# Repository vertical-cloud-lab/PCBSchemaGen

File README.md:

# PCBSchemaGen

LLM-based PCB schematic generation with automated topology verification.

# Installation

PCBSchemaGen requires:
- Python >= 3.10
- KiCad 9 (with pcbnew Python bindings)
- Node.js + `netlistsvg` (for schematic SVG generation)
- OpenAI-compatible API access

## Step 1: Install KiCad 9

Follow the official KiCad installation guide for your platform:

**https://www.kicad.org/download/**

After installation, verify KiCad and pcbnew:
```bash
kicad-cli --version
python3 -c "import pcbnew; print(pcbnew.GetBuildVersion())"
```

## Step 2: Install Python Dependencies

```bash
pip install openai pandas skidl networkx cairosvg Pillow
```

## Step 3: Install netlistsvg

SKiDL's `generate_svg()` shells out to the `netlistsvg` CLI. Without it, SVG
generation (and therefore the sample verification suite) fails. Install it with
npm (requires Node.js):

```bash
npm install -g netlistsvg
netlistsvg --help   # verify it is on your PATH
```

## Step 4: Environment Check

```bash
cd "sample design"
XDG_DATA_HOME=$(pwd)/../.xdg python3 run_samples_test.py
```

All 17 tasks should print `[PASS]`. If not, check your KiCad and `netlistsvg` installation.

# Quick Start

```bash
cd task
XDG_DATA_HOME=$(pwd)/.. python3 run.py \
  --task_id 1 \
  --model gpt-4o \
  --api_key "YOUR_API_KEY" \
  --base_url https://openrouter.ai/api/v1
```

This generates a circuit for Task 1 (voltage divider).

# API Keys

Any OpenAI-compatible API works. We recommend [OpenRouter](https://openrouter.ai):
1. Create account at https://openrouter.ai
2. Get API key from dashboard
3. Use with `--base_url https://openrouter.ai/api/v1`

You can also point directly at a provider's OpenAI-compatible endpoint. For
example, Anthropic's endpoint works with this benchmark:

```bash
cd task
OPENAI_API_KEY="YOUR_ANTHROPIC_KEY" XDG_DATA_HOME=$(pwd)/.. python3 run.py \
  --task_id 1 \
  --model claude-sonnet-4-6 \
  --base_url https://api.anthropic.com/v1/
```

Note: some newer Anthropic models (e.g. `claude-opus-4-8`) reject the
`temperature` parameter; use a model that accepts it (e.g. `claude-sonnet-4-6`)
or pass `--temperature` only with models that support it.

# Benchmark

- **Task definitions**: `benchmark.tsv` (23 tasks across 3 difficulty levels)
- **Reference designs**: `sample design/p*.py`
- **Component library**: `component.json`, `kg_component.json`
- **KiCad symbols/footprints**: `library/`

## Task Difficulty Levels

| Level | Tasks | Description |
|-------|-------|-------------|
| Easy | P1-P6 | Voltage dividers, LDOs, sensing circuits |
| Medium | P7-P16 | Half-bridge stages, gate drivers, isolated DC-DC |
| Hard | P17-P23 | Multi-switch converters (sync buck, DAB, LLC, 3-phase) |

# Example Output

The `example_output/` directory contains a successful run of Task 17 (Synchronous Buck Converter):

| File | Description |
|------|-------------|
| `attempt_1_skidl.py` | LLM-generated SKiDL code |
| `attempt_1.svg` | Circuit schematic visualization |
| `task_17_stats.json` | Run statistics (tokens, time, status) |
| `task_17_output.txt` | Full LLM output with chain-of-thought |
| `extracted_task_17.*` | Final artifacts (netlist, KiCad project) |

# Project Structure

```
PCBSchemaGen/
├── task/
│   ├── run.py                  # Single task runner
│   ├── run_feedback_trials.py  # Batch experiments
│   ├── topo/                   # Verification pipeline
│   └── prompt_template*.md     # LLM prompts
├── sample design/              # Ground truth implementations
├── library/                    # KiCad symbols & footprints
├── example_output/             # Example Task 17 output
├── benchmark.tsv               # Task definitions
├── component.json              # Component pin definitions
└── kg_component.json           # Component constraints
```

# Batch Experiments

To run multiple tasks with multiple trials:

```bash
cd task
XDG_DATA_HOME=$(pwd)/.. python3 run_feedback_trials.py \
  --task-range 1-16 \
  --trials 15 \
  --model gpt-4o \
  --api_key "YOUR_API_KEY" \
  --base_url https://openrouter.ai/api/v1 \
  --feedbacks full \
  --parallel-threads 8
```

Results are saved to `task/feedback_runs/`.

# Citation

If you find this work helpful, please cite our paper:

```bibtex
@misc{zou2026pcbschemagen,
      title={PCBSchemaGen: Constraint-Guided Schematic Design via LLM for Printed Circuit Boards (PCB)}, 
      author={Huanghaohe Zou and Peng Han and Emad Nazerian and Alex Q. Huang},
      year={2026},
      eprint={2602.00510},
      archivePrefix={arXiv},
      primaryClass={cs.AI},
      url={[https://arxiv.org/abs/2602.00510](https://arxiv.org/abs/2602.00510)}, 
}

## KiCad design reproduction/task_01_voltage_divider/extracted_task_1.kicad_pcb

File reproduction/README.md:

# Reproduction Artifacts

End-to-end run artifacts from reproducing two benchmark tasks with the full
PCBSchemaGen pipeline (LLM generation → ERC → topology verification → KiCad
artifact generation). Both runs used the OpenAI-compatible Anthropic endpoint
(`--base_url https://api.anthropic.com/v1/`) with model `claude-sonnet-4-6`.

| Task | Description | Level | Result | Attempts | Components |
|------|-------------|-------|--------|----------|-----------|
| [Task 1](task_01_voltage_divider) | Resistor divider (60 V → 3.3 V sense) | Easy | PASS | 1 | 3 |
| [Task 17](task_17_sync_buck) | Synchronous buck converter | Hard | PASS | 2 | 80 |
| [powder-doser test module](powder_doser_test_module) | Single-Pico-W bench rig ([powder-doser PR #61](https://github.com/vertical-cloud-lab/powder-doser/pull/61)) | External | PASS | 3 | 14 |

Task 17 is the paper's flagship example (compare with [`../example_output/`](../example_output)).
It passed on the second attempt: the first attempt was rejected by the topology
verifier (insufficient output capacitors) and the feedback loop drove the fix.

The [powder-doser test module](powder_doser_test_module) is a real external
design (a microcontroller/breakout board rather than a power-electronics
topology) used to exercise the pipeline outside the benchmark; see its
[README](powder_doser_test_module/README.md) for provenance and the
generation loop. Its
[`CELUS_EVALUATION.md`](powder_doser_test_module/CELUS_EVALUATION.md) assesses
how usable the generated files are for import into a component-driven
board-synthesis tool ([CELUS](https://celus.io)) and demonstrates a re-prompt
that adds the missing sourcing metadata (MPNs, datasheets, real footprints, BOM,
block diagram).

## How these were generated

```bash
cd task
OPENAI_API_KEY="YOUR_KEY" XDG_DATA_HOME=$(pwd)/.. python3 run.py \
  --task_id 1 \
  --model claude-sonnet-4-6 \
  --base_url https://api.anthropic.com/v1/ \
  --num_of_retry 3
# results land in task/p1_results/ (and task/p17_results/ for --task_id 17)
```

## Files (per task)

| File | Description |
|------|-------------|
| `extracted_task_*.png` | Schematic render (PNG, rendered from the SVG) |
| `extracted_task_*.svg` | Schematic render (vector) |
| `extracted_task_*.kicad_pcb` | KiCad PCB model |
| `extracted_task_*.kicad_pro` / `.kicad_prl` | KiCad project files |
| `extracted_task_*.net` | KiCad netlist |
| `extracted_task_*.erc` | Electrical rule check report |
| `extracted_task_*.py` | Final SKiDL source (with artifact-generation wrapper) |
| `attempt_*_skidl.py` | Per-attempt LLM-generated SKiDL code |
| `attempt_*.svg` | Per-attempt intermediate schematic render |
| `task_*_output.txt` | Full LLM response (chain-of-thought + code) |
| `task_*_stats.json` | Run statistics (tokens, timing, status) |

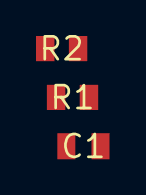
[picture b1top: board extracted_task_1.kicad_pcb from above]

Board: 2 copper layers, 3 parts (0 on the bottom side), 2 nets, no tracks yet.

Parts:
C1: 100nF; C_0805
R1: 100k; R_0805
R2: 10k; R_0805

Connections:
GND: C1.2, R2.2
VSENSE: C1.1, R1.2, R2.1

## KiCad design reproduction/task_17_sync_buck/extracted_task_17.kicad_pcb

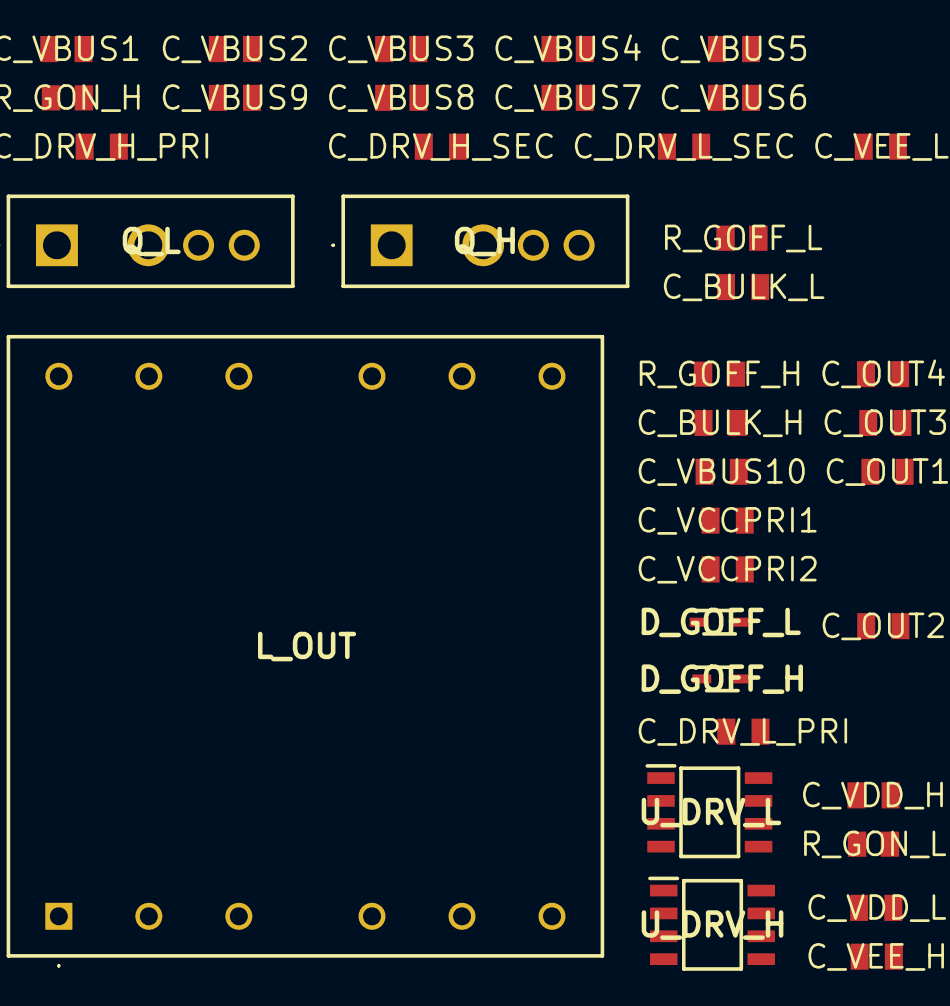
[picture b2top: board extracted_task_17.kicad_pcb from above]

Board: 2 copper layers, 37 parts (0 on the bottom side), 18 nets, no tracks yet.

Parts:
C_BULK_H: 10uF; C_0805
C_BULK_L: 10uF; C_0805
C_DRV_H_PRI: 100nF; C_0805
C_DRV_H_SEC: 100nF; C_0805
C_DRV_L_PRI: 100nF; C_0805
C_DRV_L_SEC: 100nF; C_0805
C_OUT1, C_OUT2, C_OUT3: 100uF; C_0805
C_OUT4: 100nF; C_0805
C_VBUS1, C_VBUS2, C_VBUS3, C_VBUS4, C_VBUS5, C_VBUS6, C_VBUS7, C_VBUS8: 100nF; C_0805
C_VBUS9, C_VBUS10: 10uF; C_0805
C_VCCPRI1: 100nF; C_0805
C_VCCPRI2: 10uF; C_0805
C_VDD_H: 100nF; C_0805
C_VDD_L: 100nF; C_0805
C_VEE_H: 100nF; C_0805
C_VEE_L: 100nF; C_0805
D_GOFF_H: D; BAT165
D_GOFF_L: D; BAT165
L_OUT: 10uH; Inductor_power
Q_H: IMZA65R015M2H
Q_L: IMZA65R015M2H
R_GOFF_H: 2R2; R_0805
R_GOFF_L: 2R2; R_0805
R_GON_H: 10R; R_0805
R_GON_L: 10R; R_0805
U_DRV_H: UCC5390E
U_DRV_L: UCC5390E

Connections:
DRV_H_OUT: R_GOFF_H.2, R_GON_H.1, U_DRV_H.6
DRV_L_OUT: R_GOFF_L.2, R_GON_L.1, U_DRV_L.6
GATE_H: D_GOFF_H.2, Q_H.4, R_GON_H.2
GATE_L: D_GOFF_L.2, Q_L.4, R_GON_L.2
GND_PRI: C_DRV_H_PRI.2, C_DRV_L_PRI.2, C_VCCPRI1.2, C_VCCPRI2.2, U_DRV_H.3, U_DRV_H.4, U_DRV_L.3, U_DRV_L.4
KS_H: C_DRV_H_SEC.2, C_VDD_H.2, C_VEE_H.1, Q_H.3, U_DRV_H.7
KS_L: C_DRV_L_SEC.2, C_VDD_L.2, C_VEE_L.1, Q_L.3, U_DRV_L.7
unnamed: D_GOFF_H.1, R_GOFF_H.1
unnamed: D_GOFF_L.1, R_GOFF_L.1
PGND: C_OUT1.2, C_OUT2.2, C_OUT3.2, C_OUT4.2, C_VBUS1.2, C_VBUS2.2, C_VBUS3.2, C_VBUS4.2, C_VBUS5.2, C_VBUS6.2, C_VBUS7.2, C_VBUS8.2, C_VBUS9.2, C_VBUS10.2, Q_L.2
VCC_PRI: C_DRV_H_PRI.1, C_DRV_L_PRI.1, C_VCCPRI1.1, C_VCCPRI2.1, U_DRV_H.1, U_DRV_L.1
VDD_H: C_BULK_H.1, C_DRV_H_SEC.1, C_VDD_H.1, U_DRV_H.5
VDD_L: C_BULK_L.1, C_DRV_L_SEC.1, C_VDD_L.1, U_DRV_L.5
VEE_H: C_BULK_H.2, C_VEE_H.2, U_DRV_H.8
VEE_L: C_BULK_L.2, C_VEE_L.2, U_DRV_L.8
VIN: C_VBUS1.1, C_VBUS2.1, C_VBUS3.1, C_VBUS4.1, C_VBUS5.1, C_VBUS6.1, C_VBUS7.1, C_VBUS8.1, C_VBUS9.1, C_VBUS10.1, Q_H.1
VOUT: C_OUT1.1, C_OUT2.1, C_OUT3.1, C_OUT4.1, L_OUT.7, L_OUT.8, L_OUT.9, L_OUT.10, L_OUT.11, L_OUT.12
VSW: L_OUT.1, L_OUT.2, L_OUT.3, L_OUT.4, L_OUT.5, L_OUT.6, Q_H.2, Q_L.1

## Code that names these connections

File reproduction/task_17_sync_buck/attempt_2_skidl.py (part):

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# High-side gate resistor network (turn-on / turn-off)
# ─────────────────────────────────────────────
drv_h_out = Net("DRV_H_OUT")
drv_h[6] += drv_h_out        # OUT pin of high-side driver

gate_h = Net("GATE_H")

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
# Anti-parallel diode: conducts during turn-off (gate discharging back to driver)
# D pin1=K(Anode label), pin2=A(Cathode label) per component definition
d_goff_h[2] += gate_h        # pin2(A) at gate node
d_goff_h[1] += r_goff_h[1]  # pin1(K) toward driver side
r_goff_h[2] += drv_h_out

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# Low-side gate resistor network (turn-on / turn-off)
# ─────────────────────────────────────────────
drv_l_out = Net("DRV_L_OUT")
drv_l[6] += drv_l_out        # OUT pin of low-side driver

gate_l = Net("GATE_L")

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d_goff_l = Part("test", "D", footprint="test:BAT165")
d_goff_l.ref = "D_GOFF_L"

d_goff_l[2] += gate_l        # pin2(A) at gate node
d_goff_l[1] += r_goff_l[1]  # pin1(K) toward driver side
r_goff_l[2] += drv_l_out

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# ─────────────────────────────────────────────
# Output LC filter
# ─────────────────────────────────────────────
# Power inductor: pins 1-6 = Terminal A (VSW side), pins 7-12 = Terminal B (VOUT side)
l_out = Part("test", "Inductor_power", footprint="test:Inductor_power")
l_out.ref = "L_OUT"
l_out.value = "10uH"

# Connect all A-side pins to VSW
l_out[1]  += vsw
l_out[2]  += vsw
l_out[3]  += vsw
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l_out[5]  += vsw
l_out[6]  += vsw

# Connect all B-side pins to VOUT
l_out[7]  += vout
l_out[8]  += vout
l_out[9]  += vout
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
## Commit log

2026-06-08 Initial plan
2026-06-08 Set up plan for test run of PCBSchemaGen
2026-06-08 Document required netlistsvg dependency; ignore run artifacts
2026-06-08 Commit reproduction artifacts for Task 1 and Task 17 (renders, PCB, netlists)
2026-06-08 Add powder-doser test-module reproduction (ground-truth + PCBSchemaGen LLM loop)
2026-06-09 Add CELUS suitability evaluation + executed CELUS-readiness re-prompt
2026-06-12 Verify powder-doser CELUS datasheets against project vendor files + sources
2026-06-12 Fix stray soft hyphen in belfuse.com reference
